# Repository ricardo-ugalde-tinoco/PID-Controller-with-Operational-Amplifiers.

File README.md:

Design of a PID controller using different arrays of operational amplifiers in order to be able to regulate the temperature of a freezer.
For this application an LM35 sensor was used, because it is a sensor that does not require to be connected to a microprocessor to perform the temperature measurement and delivers an analogue output signal.

In addition, LM741 operational amplifiers were used, these general purpose operational amplifiers have a high performance in temperatures from -55° C to 125° C, another reason why this model was used was the fact that it has a protection against overloads at the input and output of each power supply pin.

Finally, a power stage was used to amplify the current in order to supply an actuator capable of temperature correction. However, the actuator was not included because the main focus is on the development of the controller.
In this power stage, BC337 (NPN) and BC327 (PNP) bipolar transistors were used, as they are a common model in small motor driver applications.

If you wish to consult the calculations, a PDF document with all the calculations will be attached.

To check the correct operation of the circuit, simulations were carried out in LTSpice. As the one shown below where I try to obtain a gain of 10 at a voltage of 0.5 Volts.

In the project scheme I wrote down all the formulas needed to find the value of each of the resistors and components used in the conventional notation of the diagrams.
As shown in the following image.

This practice is very useful to describe more precisely your connections and the sequence to develop your circuit.

Model of the completed PCB.

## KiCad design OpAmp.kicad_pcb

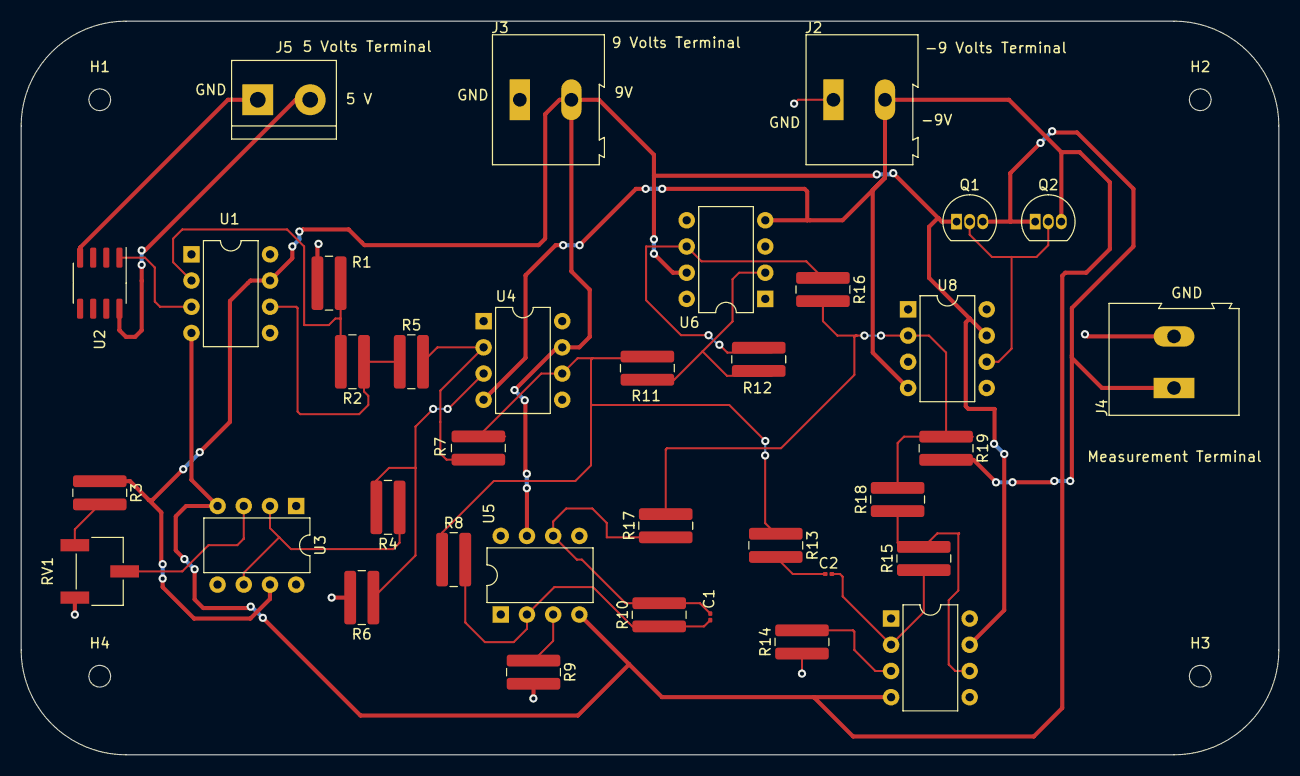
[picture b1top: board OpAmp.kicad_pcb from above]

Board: 2 copper layers, 121.9 x 71.1 mm, 40 parts (0 on the bottom side), 25 nets.

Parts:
C1: 100u; C_0201_0603Metric
C2: 0.1u; C_0201_0603Metric
H1, H2, H3, H4: MountingHole; MountingHole_2.1mm
J2, J3, J4: Screw_Terminal_01x02; TerminalBlock_Altech_AK300-2_P5.00mm
J5: Screw_Terminal_01x02; TerminalBlock_bornier-2_P5.08mm
Q1: BC337; TO-92_Inline
Q2: BC327; TO-92_Inline
R1: 1K; R_1020_2550Metric
R2: 9K; R_1020_2550Metric
R3: 160; R_1020_2550Metric
R4, R5, R6, R7, R16, R17, R18, R19: 1k; R_1020_2550Metric
R8: 289.35; R_1020_2550Metric
R9: 263.23; R_1020_2550Metric
R10: 3674.745; R_1020_2550Metric
R11: 20; R_1020_2550Metric
R12: 4338.2; R_1020_2550Metric
R13: 125; R_1020_2550Metric
R14, R15: 1592.5; R_1020_2550Metric
RV1: 200; Potentiometer_Bourns_3269W_Vertical
U1, U3, U4, U5, U6, U7, U8: LM741; DIP-8_W7.62mm
U2: LM35-D; SOIC-8_3.9x4.9mm_P1.27mm

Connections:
+5V: J5.2, U2.8 (+V_{S})
+9V: J3.2, Q1.1 (C), R3.1, U1.7 (V+), U3.7 (V+), U4.7 (V+), U5.7 (V+), U6.7 (V+), U7.7 (V+), U8.7 (V+)
-9V: J2.2, Q2.3 (E), U1.4 (V-), U3.4 (V-), U4.4 (V-), U5.4 (V-), U6.4 (V-), U7.4 (V-), U8.4 (V-)
GND: J2.1, J3.1, J4.2, J5.1, R1.2, R6.2, R9.2, R14.1, RV1.3, U2.4 (GND), U6.3 (+), U8.3 (+)
unnamed: C1.2, R10.2, R17.1, U5.6
unnamed: C2.1, R13.2
unnamed: J4.1, Q1.3 (E), Q2.1 (C), R19.2
unnamed: Q1.2 (B), Q2.2 (B), U8.6
unnamed: R2.1, R5.1, U1.6
unnamed: R3.2, RV1.1
unnamed: R7.2, R8.1, R11.2, R13.1, U4.6
unnamed: R12.2, R16.1, U6.6
unnamed: R15.2, R18.1, U7.6
unnamed: U1.3 (+), U2.1 (V_{OUT})
unnamed: R1.1, R2.2, U1.2 (-)
unnamed: RV1.2, U3.3 (+)
unnamed: R4.1, U3.2 (-), U3.6
unnamed: R4.2, R6.1, U4.3 (+)
unnamed: R5.2, R7.1, U4.2 (-)
unnamed: R9.1, U5.3 (+)
unnamed: C1.1, R8.2, R10.1, U5.2 (-)
unnamed: R11.1, R12.1, U6.2 (-)
unnamed: R14.2, U7.3 (+)
unnamed: C2.2, R15.1, U7.2 (-)
unnamed: R16.2, R17.2, R18.2, R19.1, U8.2 (-)

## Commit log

2024-01-16 README.md
